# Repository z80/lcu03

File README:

Stackable stepper motor controller.

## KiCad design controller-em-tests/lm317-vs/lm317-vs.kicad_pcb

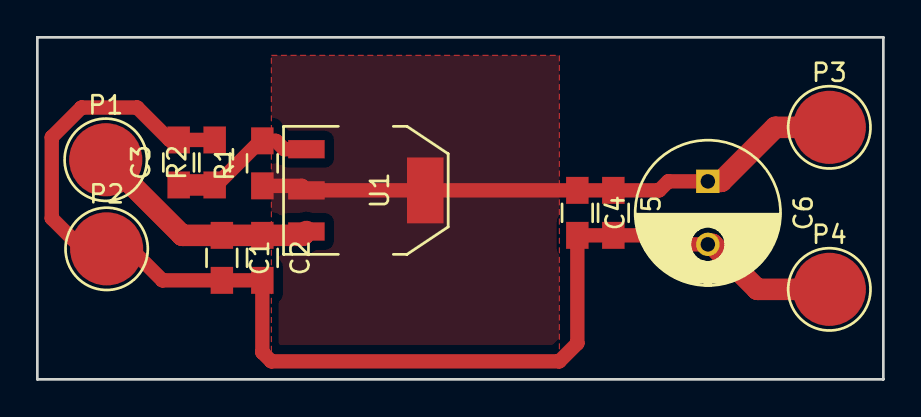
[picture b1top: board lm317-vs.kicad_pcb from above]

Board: 2 copper layers, 47.0 x 19.0 mm, 13 parts (0 on the bottom side), 4 nets.

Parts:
C1, C5: 4u7; C_0805_HandSoldering
C2, C3, C4: 100n; C_0805_HandSoldering
C6: CP; C_Radial_D8_L11.5_P3.5
P1: in-15v; 1pin
P2, P4: gnd; 1pin
P3: out-12v; 1pin
R1: 820R; C_0805_HandSoldering
R2: 6k8; C_0805_HandSoldering
U1: LM317EMP; SOT-223

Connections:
GND: C1.2, C2.2, C3.2, C4.2, C5.2, C6.2, P2.1, P4.1, R2.2
unnamed: C1.1, C2.1, P1.1, U1.3
unnamed: C3.1, R1.2, R2.1, U1.1
unnamed: C4.1, C5.1, C6.1, P3.1, R1.1, U1.2

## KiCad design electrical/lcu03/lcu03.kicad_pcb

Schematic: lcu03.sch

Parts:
C1, C4, C5, C8, C9, C10, C11, C14, C15, C23, C24, C26: 100n; C_0805
C2, C3: 18p; C_0805
C6, C7, C12, C13, C18, C21: 4u7; C_0805
C16: 10n; C_0805
C19: 2n2; C_0805
C22, C25: 680u; C_Radial_D10_L20_P5
D1, D2: LED; LED-3MM
D3, D4: 1n5819; Diode_DO-41_SOD81_Horizontal_RM10
L1: 10uH; R_1206_HandSoldering
L2: 100uH; my_inductance
P1, P2, P3, P4, P16, P17: screw; MountingHole_3mm
P5: ext-1; Pin_Header_Straight_1x08
P6: ~rst~; Measurement_Point_Round-TH_Small
P7: mode; Pin_Header_Straight_1x02
P8: ext-2; Pin_Header_Straight_1x08
P9: USB_B
P10: swd; Pin_Header_Straight_1x03
P11, P12, P13: stepper_conn; my-JST_B4B-PH-SM4-TB
Q1, Q3: bc857; SOT-23
Q2: bc847; SOT-23
Q4: ntd18n06l; my-DPAK
R1, R4, R5, R7, R8, R9, R10, R11, R19, R27, R47: 10k 5%; R_0805
R2, R3, R13, R20, R25, R34, R36: 1k 5%; R_0805
R6: 100 5%; R_0805
R12: 0.15 5%; C_1206
R14, R15: ferrite bead; R_0805
R16: 6k2 5%; R_0805
R17: 47k 5%; R_0805
R18, R21, R22, R23, R33, R35: 33k 5%; R_0805
R24: 10 5%; Resistor_Horizontal_RM10mm
R26: 100k 5%; R_0805
R28, R29, R30, R31, R32: 0; R_0805
U1: crystal-4pin; CRYSTAL-SMD-5x3
U2: CP2102
U3: m24c02; SOIC-8_3.9x4.9mm_Pitch1.27mm
U4: NCP3063; SOIC-8_3.9x4.9mm_Pitch1.27mm
U5: my-NCP1117ST50T3G; SOT-223
U6: ts881; SOT-23-5
U7: lb1930mc
U10: MCP1703T-3302E/CB; SOT-23
stm1: STM32F103CBT6; LQFP48

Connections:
/Vbus: C13.1, C15.1, P5.1, P9.1 (VCC), P12.1, P13.1, R12.2, R15.2, R17.1, U2.8 (Vbus), U4.6 (vcc)
/boot0: P7.2, R5.2, stm1.44 (BOOT0)
/boot1: R7.2, stm1.20 (PB2/BOOT1)
/clk-in: C2.2, U1.3 (xtal2), stm1.5 (PD0/OSC_IN)
/clk-out: R6.1, stm1.6 (PD1/OSC_OUT)
/cts: U2.23 (CTS), stm1.33 (PA12/USART1_RTS/USBDP)
/d+: P9.3 (D+), U2.4 (D+)
/d-: P9.2 (D-), U2.5 (D-)
/ext-power-flag: U6.1 (out), stm1.45 (PB8/TIM4_CH3^I2C1_SCL)
/gpio-0: P8.5, stm1.29 (PA8/USART1_CK/MCO)
/gpio-1: P8.6, stm1.28 (PB15/SPI2_MOSI)
/gpio-2: P8.7, stm1.27 (PB14/SPI2_MISO/USART3_RTS)
/gpio-3: P8.8, stm1.19 (PB1/ADC_IN9/TIM3_CH4)
/hall1: R33.2, R34.2, stm1.15 (PA5/SPI1_SCK/ADC_IN5)
/hall2: R35.2, R36.2, stm1.25 (PB12/SPI2_NSS/I2C2_SMBA/USART3_CTS)
/i2c1-scl: P5.3, R10.2, U3.6 (Scl), stm1.42 (PB6/I2C1_SCL/TIM4_CH1^USART1_TX)
/i2c1-sda: P5.4, R11.2, U3.5 (Sda), stm1.43 (PB7/I2C1_SDA/TIM4_CH3^USART1_RX)
/led-0: R2.1, stm1.3 (PC14/OSC32_IN)
/led-1: R3.1, stm1.2 (PC13/TAMPER-RTC)
/reg-fb: C16.1, C24.1, C25.1, D4.1 (K), L1.2, P8.3, R14.2, R16.1
/rts: U2.24 (RTS), stm1.32 (PA11/USART1_CTS/USBDM)
/rx-2: P5.7, R4.2, stm1.13 (PA3/USART2_RX/ADC_IN3/TIM2_CH4)
/rxd: R47.2, U2.25 (RXD), stm1.30 (PA9/USART1_TX)
/shutter-a: U7.3 (in1), stm1.10 (PA0/WKUP/USART2_CTS/ADC_IN0/TIM2_CH1_ETR)
/shutter-b: U7.4 (in2), stm1.4 (PC15/OSC32_OUT)
/shutter-out-a: R24.2, R32.2, U7.9 (out1)
/shutter-out-b: P11.3, P11.4, U7.7 (out2)
/stepper-subcircuit-1/Vbb: C22.1, C26.1, L1.1, U7.1 (Vcc); also elsewhere on the board
/stepper-subcircuit-1/dir: stm1.22 (PB11/I2C2_SDA/USART3_RX^TIM2_CH4); also elsewhere on the board
/stepper-subcircuit-1/ms1: R28.2, R29.1; also elsewhere on the board
/stepper-subcircuit-1/ms2: R30.2, R31.1; also elsewhere on the board
/stepper-subcircuit-1/ref: R23.2, R26.2, R27.1; also elsewhere on the board
/stepper-subcircuit-1/step: stm1.18 (PB0/ADC_IN8/TIM3_CH3); also elsewhere on the board
/stepper-subcircuit-1/~enable~: stm1.21 (PB10/I2C2_SCL/USART3_TX^TIM2_CH3); also elsewhere on the board
/stepper-subcircuit-1/~reset~: stm1.17 (PA7/SPI1_MOSI/ADC_IN7/TIM3_CH2); also elsewhere on the board
/stepper-subcircuit-1/~sleep~: stm1.16 (PA6/SPI1_MISO/ADC_IN6/TIM3_CH1); also elsewhere on the board
/stepper-subcircuit-2/dir: stm1.14 (PA4/SPI1_NSS/ADC_IN4/USART2_CK); also elsewhere on the board
/stepper-subcircuit-2/step: stm1.11 (PA1/USART2_RTS/ADC_IN1/TIM2_CH2); also elsewhere on the board
/suspend: U2.12 (SUSPEND), stm1.41 (PB5/I2C1_SMBA^TIM3_CH2/SPI1_MOSI)
/swd-clk: P10.3, stm1.37 (JTCK/SWCLK^PA14)
/swd-io: P10.1, stm1.34 (JTMS/SWDIO^PA13)
/tx-2: P5.6, stm1.12 (PA2/USART2_TX/ADC_IN2/TIM2_CH3)
/txd: U2.26 (TXD), stm1.31 (PA10/USART1_RX)
/~high-current~: R19.1, R20.2, stm1.26 (PB13/SPI2_SCK/USART3_CTS)
/~mcu-rst~: C4.1, P6.1, R8.2, stm1.7 (NRST)
/~wc~: R9.2, U3.7 (~WC~), stm1.46 (PB9/TIM4_CH4^I2C1_SDA)
GND: C1.2, C2.1, C3.2, C4.2, C5.2, C6.2, C7.2, C8.2, C9.2, C10.2, C11.2, C12.2, C13.2, C14.2, C15.2, C18.2, C19.2, C21.2, C22.2, C23.2, C24.2, C25.2, C26.2, D1.2 (A), D2.2 (A), P1.1, P2.1, P3.1, P4.1, P5.2, P5.5, P5.8, P8.2, P8.4, P9.4 (GND), P9.5 (shield), P10.2, P11.0 (pad), P12.0 (pad), P12.2, P13.0 (pad), P13.2, P16.1, P17.1, Q3.3 (C), Q4.3 (S), R5.1, R7.1, R13.2, R18.2, R22.2, R25.2, R27.2, R29.2, R31.2, R33.1, R35.1, U1.2, U1.4, U2.0 (Gnd), U2.3 (Gnd), U3.1 (E0), U3.2 (E1), U3.3 (E2), U3.4 (Vss), U4.4 (gnd), U5.1 (GND), U6.2 (Vcc-), U7.5 (s-gnd), U7.6 (p-gnd), U10.1 (Gnd), stm1.8 (Vssa), stm1.23 (Vss_1), stm1.35 (Vss_2), stm1.47 (Vss_3); also elsewhere on the board
unnamed: C1.1, R1.2, U2.9 (~RST~)
unnamed: C3.1, R6.2, U1.1 (xtal)
unnamed: C7.1, U2.18 (Vpp/nc)
unnamed: C16.2, R13.1, R16.2, U4.5 (comp)
unnamed: C18.1, D3.1 (K), U5.3 (VI), U10.3 (Vin)
unnamed: C19.1, U4.3 (tcap)
unnamed: D1.1 (K), R2.2
unnamed: D2.1 (K), R3.2
unnamed: D3.2 (A), R14.1, R15.1
unnamed: D4.2 (A), L2.2, Q4.2 (D), Q4.4 (D)
unnamed: L2.1, R12.1, U4.1 (swc), U4.7 (ipk)
unnamed: P11.1, P11.2, R24.1, R32.1
unnamed: P12.3, R34.1
unnamed: P13.3, R36.1
unnamed: Q1.1 (B), R20.1
unnamed: Q1.3 (C), R23.1
unnamed: Q2.1 (B), Q2.3 (C), Q3.1 (B), R25.1, U4.2 (swe)
unnamed: Q2.2 (E), Q3.2 (E), Q4.1 (G)
unnamed: R17.2, R18.1, U6.3 (in+)
unnamed: R21.2, R22.1, U6.4 (in-)
VDD: C5.1, C6.1, C8.1, C9.1, C10.1, C11.1, C12.1, C14.1, C21.1, C23.1, P7.1, P8.1, Q1.2 (E), R1.1, R4.1, R8.1, R9.1, R10.1, R11.1, R19.2, R21.1, R26.1, R28.1, R30.1, R47.1, U2.6 (Vdd), U2.7 (REGIN), U2.10 (nc), U2.13 (nc), U2.14 (nc), U2.15 (nc), U2.16 (nc), U2.17 (nc), U2.19 (nc), U2.20 (nc), U2.21 (nc), U2.22 (nc), U3.8 (Vcc), U5.2 (VO), U5.4 (VO), U6.5 (Vcc+), U10.2 (Vout), stm1.1 (Vbat), stm1.9 (Vdda), stm1.24 (Vdd_1), stm1.36 (Vdd_2), stm1.48 (Vdd_3); also elsewhere on the board

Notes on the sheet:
+9V
Just for compatibility with CP2109 and may be not installed for CP2102. 4u7 capacitor.
USB scheme.
If Vbus drops too low consider poweroff. Switch to higher voltage from boost regulator to live longer.
This diode prevents sucking voltage back from here when power is off.
Only one 0R resistor should be soldered. I'm slightly in doubt if it's OK to provide 9V to such tiny sot23 regulator input.
According to datasheet driver's input doesn't need voltage source at the input. Voltage divider is ok.
No need in mosfet switch turning off all power circuits as their consumption in standby mode is 10uA+10uA+10uA.
Hall sensors MUST be powered from USB directly as their working minimum voltage is 3.8V (!!!)
Middle of 3.3V. E.i. 1.65V.
Voltage matches 1.65V when Vbus drops to 4V.
Filtering capacitors are located on sensor PCBs.
This one in bigger package to resist heating.
And instead of 0R install ferrite bead in 0805 packaging. digiket pn: 445-172904-1-ND.
Changed this one to ncp1117 in sot-223 case because 1) it was very hot and sot-223 should dissipate better then sot-23 2) it is $0.20 cheaper.
According to datasheet this one is mandatory for stability.
This one is for backward compatibility. As it is known that with it board worked. If new stabilizer causes problems it could be replaced with this one without PCB redesign.

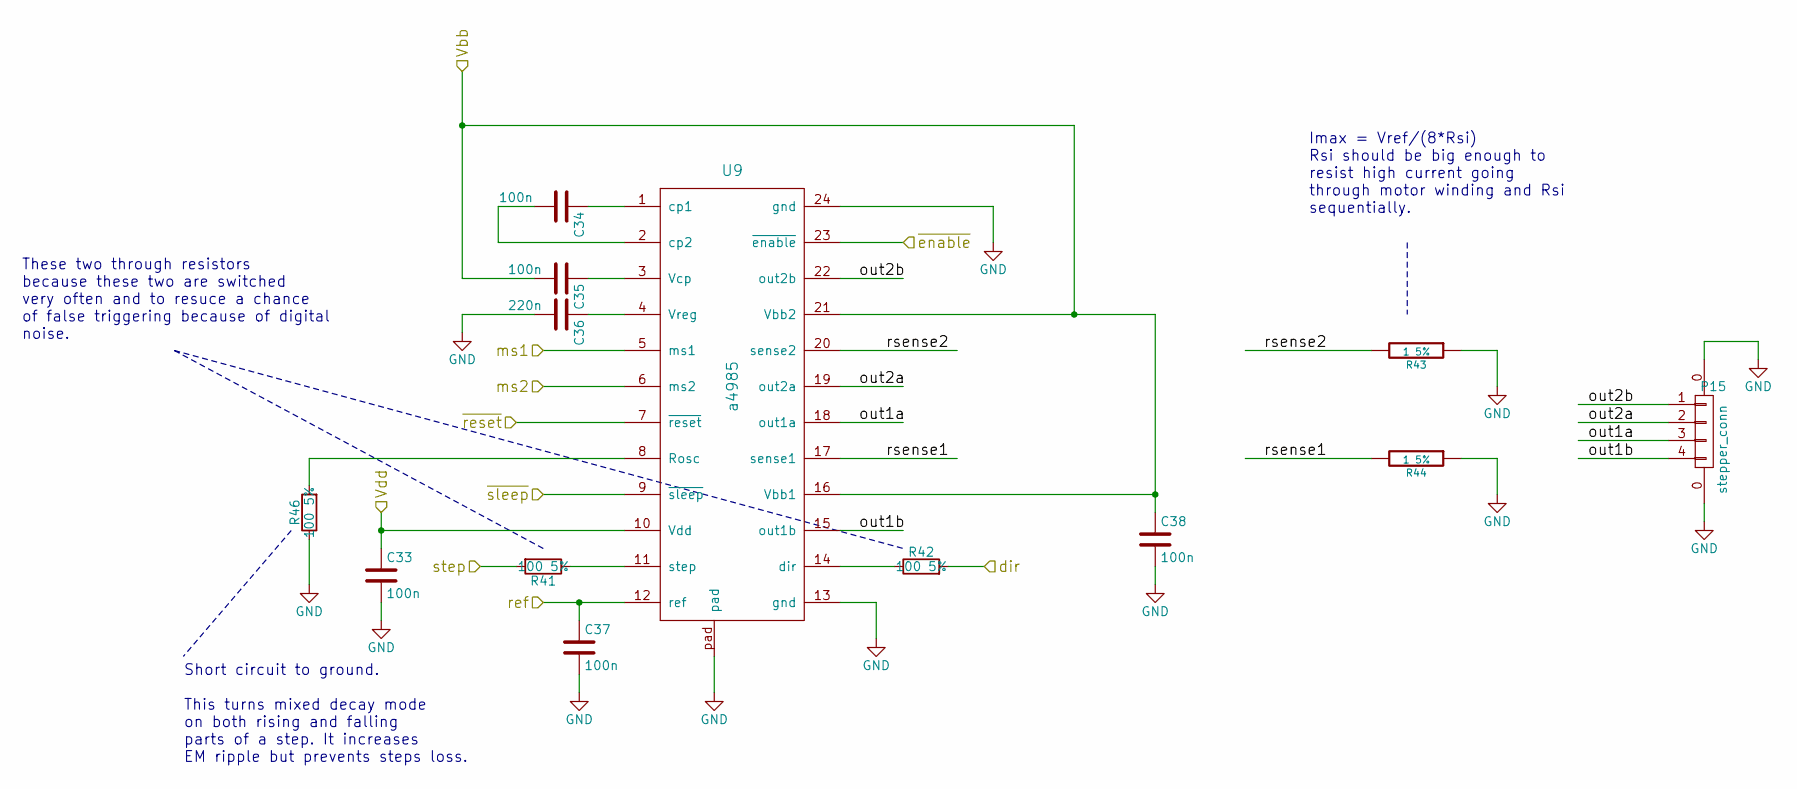
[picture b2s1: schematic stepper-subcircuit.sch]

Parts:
C27, C28, C29, C31, C32: 100n; C_0805
C30: 220n; C_0805
P14: stepper_conn; my-JST_B4B-PH-SM4-TB
R37, R38, R45: 100 5%; R_0805
R39, R40: 1 5%; R_0805
U8: a4985

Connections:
/stepper-subcircuit-1/Vbb: C29.2, C32.1, U8.16 (Vbb1), U8.21 (Vbb2); also elsewhere on the board
/stepper-subcircuit-1/dir: R38.2; also elsewhere on the board
/stepper-subcircuit-1/ms1: U8.5 (ms1); also elsewhere on the board
/stepper-subcircuit-1/ms2: U8.6 (ms2); also elsewhere on the board
/stepper-subcircuit-1/out1a: P14.3, U8.18 (out1a)
/stepper-subcircuit-1/out1b: P14.4, U8.15 (out1b)
/stepper-subcircuit-1/out2a: P14.2, U8.19 (out2a)
/stepper-subcircuit-1/out2b: P14.1, U8.22 (out2b)
/stepper-subcircuit-1/ref: C31.1, U8.12 (ref); also elsewhere on the board
/stepper-subcircuit-1/rsense1: R40.2, U8.17 (sense1)
/stepper-subcircuit-1/rsense2: R39.2, U8.20 (sense2)
/stepper-subcircuit-1/step: R37.2; also elsewhere on the board
/stepper-subcircuit-1/~enable~: U8.23 (~enable~); also elsewhere on the board
/stepper-subcircuit-1/~reset~: U8.7 (~reset~); also elsewhere on the board
/stepper-subcircuit-1/~sleep~: U8.9 (~sleep~); also elsewhere on the board
GND: C27.2, C30.2, C31.2, C32.2, P14.0 (pad), R39.1, R40.1, R45.1, U8.13 (gnd), U8.24 (gnd), U8.pad; also elsewhere on the board
unnamed: C28.1, U8.1 (cp1)
unnamed: C28.2, U8.2 (cp2)
unnamed: C29.1, U8.3 (Vcp)
unnamed: C30.1, U8.4 (Vreg)
unnamed: R37.1, U8.11 (step)
unnamed: R38.1, U8.14 (dir)
unnamed: R45.2, U8.8 (Rosc)
VDD: C27.1, U8.10 (Vdd); also elsewhere on the board

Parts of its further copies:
C33, C34, C35, C37, C38: 100n; C_0805
C36: 220n; C_0805
P15: stepper_conn; my-JST_B4B-PH-SM4-TB
R41, R42, R46: 100 5%; R_0805
R43, R44: 1 5%; R_0805
U9: a4985

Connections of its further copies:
/stepper-subcircuit-1/Vbb: C35.2, C38.1, U9.16 (Vbb1), U9.21 (Vbb2); also elsewhere on the board
/stepper-subcircuit-1/ms1: U9.5 (ms1); also elsewhere on the board
/stepper-subcircuit-1/ms2: U9.6 (ms2); also elsewhere on the board
/stepper-subcircuit-1/ref: C37.1, U9.12 (ref); also elsewhere on the board
/stepper-subcircuit-1/~enable~: U9.23 (~enable~); also elsewhere on the board
/stepper-subcircuit-1/~reset~: U9.7 (~reset~); also elsewhere on the board
/stepper-subcircuit-1/~sleep~: U9.9 (~sleep~); also elsewhere on the board
/stepper-subcircuit-2/dir: R42.2; also elsewhere on the board
/stepper-subcircuit-2/out1a: P15.3, U9.18 (out1a)
/stepper-subcircuit-2/out1b: P15.4, U9.15 (out1b)
/stepper-subcircuit-2/out2a: P15.2, U9.19 (out2a)
/stepper-subcircuit-2/out2b: P15.1, U9.22 (out2b)
/stepper-subcircuit-2/rsense1: R44.2, U9.17 (sense1)
/stepper-subcircuit-2/rsense2: R43.2, U9.20 (sense2)
/stepper-subcircuit-2/step: R41.2; also elsewhere on the board
GND: C33.2, C36.2, C37.2, C38.2, P15.0 (pad), R43.1, R44.1, R46.1, U9.13 (gnd), U9.24 (gnd), U9.pad; also elsewhere on the board
unnamed: C34.1, U9.1 (cp1)
unnamed: C34.2, U9.2 (cp2)
unnamed: C35.1, U9.3 (Vcp)
unnamed: C36.1, U9.4 (Vreg)
unnamed: R41.1, U9.11 (step)
unnamed: R42.1, U9.14 (dir)
unnamed: R46.2, U9.8 (Rosc)
VDD: C33.1, U9.10 (Vdd); also elsewhere on the board

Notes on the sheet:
Short circuit to ground. This turns mixed decay mode on both rising and falling parts of a step. It increases EM ripple but prevents steps loss.
Imax = Vref/(8*Rsi) Rsi should be big enough to resist high current going through motor winding and Rsi sequentially.
These two through resistors because these two are switched very often and to resuce a chance of false triggering because of digital noise.

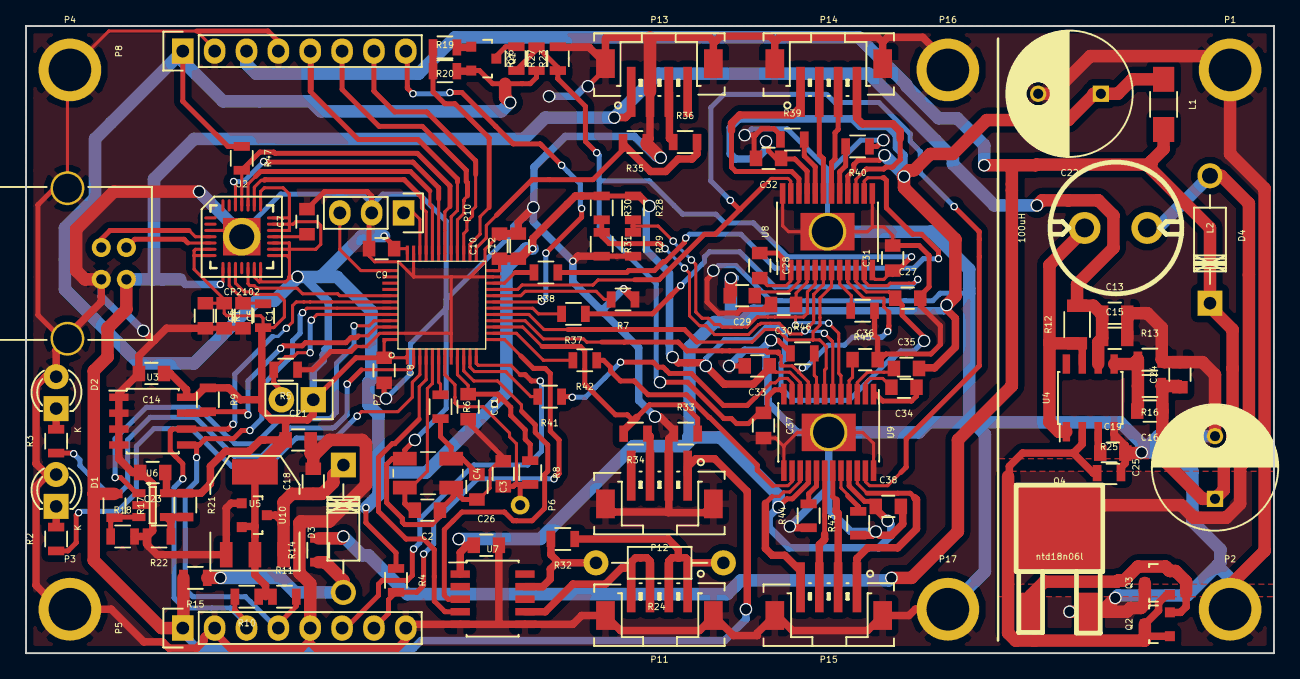
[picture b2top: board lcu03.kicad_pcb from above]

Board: 2 copper layers, 99.5 x 50.0 mm, 121 parts (0 on the bottom side), 94 nets.

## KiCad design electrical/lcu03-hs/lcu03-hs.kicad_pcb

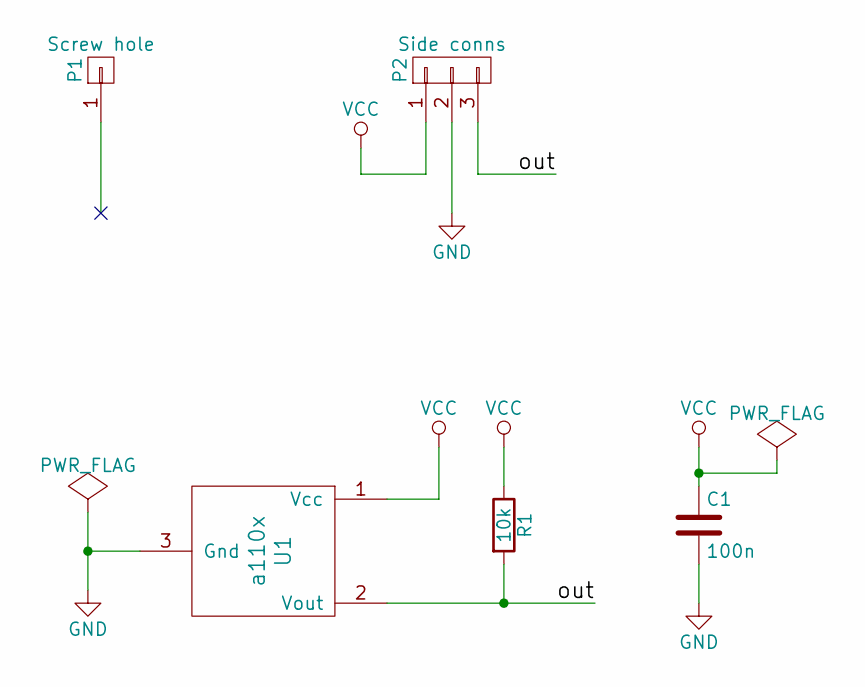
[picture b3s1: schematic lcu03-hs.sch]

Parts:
C1: 100n; C_0603
P1: Screw hole; 1pin
P2: Side conns; Pin_Header_Angled_1x03
R1: 10k; R_0603
U1: a110x; SOT-23-wide

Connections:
/out: P2.3, R1.2, U1.2 (Vout)
GND: C1.2, P2.2, U1.3 (Gnd)
VCC: C1.1, P2.1, R1.1, U1.1 (Vcc)

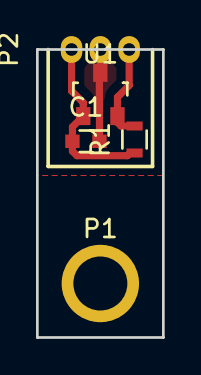
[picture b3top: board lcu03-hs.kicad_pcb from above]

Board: 2 copper layers, 7.0 x 16.0 mm, 5 parts (0 on the bottom side), 3 nets.

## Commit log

2015-12-09 Designing pcb...
2015-12-09 "lib" files are component library files in KiCad.
2015-12-09 Temporarilt remove ".gitignore" to protect myself from unsaved files.
2015-12-09 Added comparator as a library.
2015-12-09 It looks like completed schematics.
2015-12-09 Added specific socket used for stepper motors and for sensors.
2015-12-14 Added KiCad footprint libraries in file system as there are some troubles with access to them via github.com.
2015-12-15 Looks like done with assigning footprints.
2015-12-15 Started placing components.
2015-12-17 Finished routing.
2015-12-17 Generated drill and fabrication files.
2015-12-21 Added firmware.
2015-12-21 Firmware code compiles.
2015-12-23 Indented ordered items.
2015-12-29 Wiring schemes.
2015-12-31 Datasheet on a chip for high current stepper motors.
2015-12-31 Changed cable length.
2016-01-02 Added moto and shutter control files.
2016-01-03 Filling motor control file.
2016-01-05 Added appropriate peripherials.
2016-01-07 Made code compilable. And shifted firmware start to flash memory start.
2016-01-07 Shutter works but due to some reason boost power supply doesn't provide enough current. With only microcontroller on it gives only about 4.6V. And it is strange as at input there is bigger voltage. A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
2016-01-07 Modificatins list.
2016-01-07 Decreased even more shutter switching period.
2016-01-07 Working on motors implementation.
2016-01-07 PWM3 works, PWM2 due to some reason doesn't work.
2016-01-07 Snapshot before trying 3.0.4.
2016-01-07 3.0.4 copied.
2016-01-08 Working on motor algorithm.
2016-01-08 Decreased even more shutter active period.
2016-01-08 Reimplemented stepping control via pure timers. It is because I still can't run PWM2. While PWM3 works perfectly.
2016-01-08 In such combination motor works.
2016-01-08 Still works but counts steps in wrong way probably.
2016-01-08 One motor works perfectly.
2016-01-08 Both motors work.
2016-01-08 Hall sensors work.
2016-01-08 Just inserted cpuio interface functions.
2016-01-08 Adjusted IO code on computer side.
2016-01-08 LED and motor functions checked. USB IO works for this implementation without hardware flow control.
2016-01-09 Started making settings dialog.
2016-01-09 Copied modelling files from voltamp.git.
2016-01-10 According to modeling good combination is upper resistor 220, capacitor 100n, lower resistor 1k. It will allow MOSFET to open and will make open-close and close-open transitions close to region where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
2016-01-12 Done with filling settings dialog.
2016-01-12 Fixing errors...
2016-01-13 Made 8x step division when moving. And usual 1:1 counting. E.i. one step is 8 substeps. So everything is as before.
2016-01-13 Engaged bootloader.
2016-01-13 Driver.
2016-01-13 Debugging software.
2016-01-13 Inserted installer.
2016-01-14 Included fixtures in User comments layer.
2016-01-14 Started eeprom implementation.
2016-01-14 Marked another unused capacitor.
2016-01-14 Designing EEPROM interface.
2016-01-14 Automatic position adjustment if sensor is detected.
2016-01-14 Debugging emergency writes.
2016-01-14 Access to EEPROM from CPU.
2016-01-15 Prepared EEPROM debugging.
2016-01-15 Motor position save works. Shutter switches 3 times. And it also works.
2016-01-15 Made default addresses in EEPROM start with page start.
2016-01-15 Implemented All settings inside EEPROM.
2016-01-15 Returned CPU maximum speed. If not at maximum failed to reply CPU during motor motion.
2016-01-15 Introduced software version. Added move arrows.
2016-01-15 Adjusted "About" dialog.
2016-01-15 Started remote control.
2016-01-15 Inserted remote control into GUI software.
2016-01-16 Implemented remote control library.
2016-01-16 Adjusted port number.
2016-01-16 Introduced serial number assigning piece of software.
2016-01-16 Reconfigured firmware for bootloader usage.
2016-01-16 Need to redesign remote controls via signal/slot. Remote invocation takes place in a separate thread. This causes problems in GUI.
2016-01-17 FPGA/CPLD updated info. (It is not related to LCU03, just need some place to store this usefull information.)
2016-01-17 Added SIP-4.17 distributive.
2016-01-17 Added IWDG to bootloader.
2016-01-17 Adding python binding via Boost.
2016-01-18 Modified serial number assignment utility.
2016-01-18 Modified installer software.
2016-01-18 Devices assigned.
2016-01-18 Started help system.
2016-01-18 Adjusted settings: removed autofocus from a button added.
2016-01-19 Working on help system.
2016-01-19 Help window copiles but doesn't show anything.
2016-01-21 It shows something!
2016-01-21 Working on help for the software.
2016-01-21 Text is shown but images and style don't...
2016-01-21 Html and images are ok. But css is not applied.
2016-01-21 Added toolTip to firmware upgrade button in settings dialog.
2016-01-21 Changed the default folder to 1.0.0 instead of 0.0.1-alpha.
2016-01-26 Adjusted power inpup.
2016-01-26 Version is changed to 1.0.1.
2016-02-01 Microcontroller documentation.
2016-02-10 Replaced linear regulator, changed socket footprints and implemented all improvements from "zzz.txt" file.
2016-02-11 Finished routing. Going to apply a few beautifications.
2016-02-11 Finished beautifications. Generated gerber files.
2016-02-11 Prepared files for OSHPark. Called it lcu03-v2.
2016-02-11 Changed component value.
2016-02-12 Debugged projects. Actually, firmwares are supposed to be the same.
2016-02-15 Putting motors in reset mode when not spinning.
2016-02-16 Devreased default motor speed. Made "sleep" mode on when motors are not spinning.
2016-02-16 Adjusted position adjustment procedure.
2016-02-16 Icon version is adjusted. Steps are read back after setting.
2016-02-16 Increased motors speed as before. Problem with position unstability disappeared.
2016-02-16 Removed extra "F1" label in help falling menu.
2016-02-17 Info related to controllers hardware adjustments.
2016-02-23 Added some comments just for reference in future.
2016-02-23 Changed power supply circuit. Removed transistors and introduced 100R resistor in series.
2016-02-23 Exported most recent gerbers.
2016-02-24 Prepared v3 for OSHPark.
2016-03-24 Added comments.
2016-03-24 1) If motor is within 5 steps from desired position it is not displaced. 2) Lost focus event is prevented from causing editingFinished() to be raised.
2016-03-24 Changed version to 1.0.3 in installer.
2016-03-25 Removed unnecessary forced loose of control focus.
2016-04-17 Looks like fixed my own I2C slave mode edit.
2016-04-17 Started motors control over I2C.
2016-04-17 Added queued mode to I2C in os.
2016-04-17 Adding i2C extension to commands.
2016-04-21 Implemented test.
2016-04-21 Python binding from old project.
2016-04-22 Debugging.
2016-04-22 Debugging...
2016-04-23 Here under Linux debuggs properly. Nothing crashes. At least for the moment. Managed to debug up to semaphore reset. It is not allowed to reset it to negative values. May be have to remake this synch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
2016-04-24 Added stopping functionality.
2016-04-24 Started inserting quering FIFO free space in interaction library.
2016-04-25 Added LEDs for status indication.
2016-04-25 Conditional current change.
2016-04-25 Started secondary controller's firmware.
2016-05-10 Fan power supply.
2016-05-13 Moved to separate directory.
2016-05-13 EM radiation data analysis.
2016-05-14 Added more data measurements.
2016-05-16 Data comparison for various antenna configurations and positions between regular and improved units.
2016-05-18 Both firmware work. Going to turn I2C on.
2016-05-20 I2C communication using normal protocol, the same one used with serial communication works.
2016-06-10 Device #04 added.
2016-06-10 Controller EM data and analysis R file.
2016-07-22 Changed software version to 1.0.4.a
2016-08-01 Just rebuilt.
2016-08-01 Fixed a few errors. Now it works!
2016-08-01 Improved string formatting.
2016-08-09 Added readme to show description.
2019-03-23 This one is supposed to work properly. But bootloader is disabled.
2019-03-23 Reenabled bootloader.
